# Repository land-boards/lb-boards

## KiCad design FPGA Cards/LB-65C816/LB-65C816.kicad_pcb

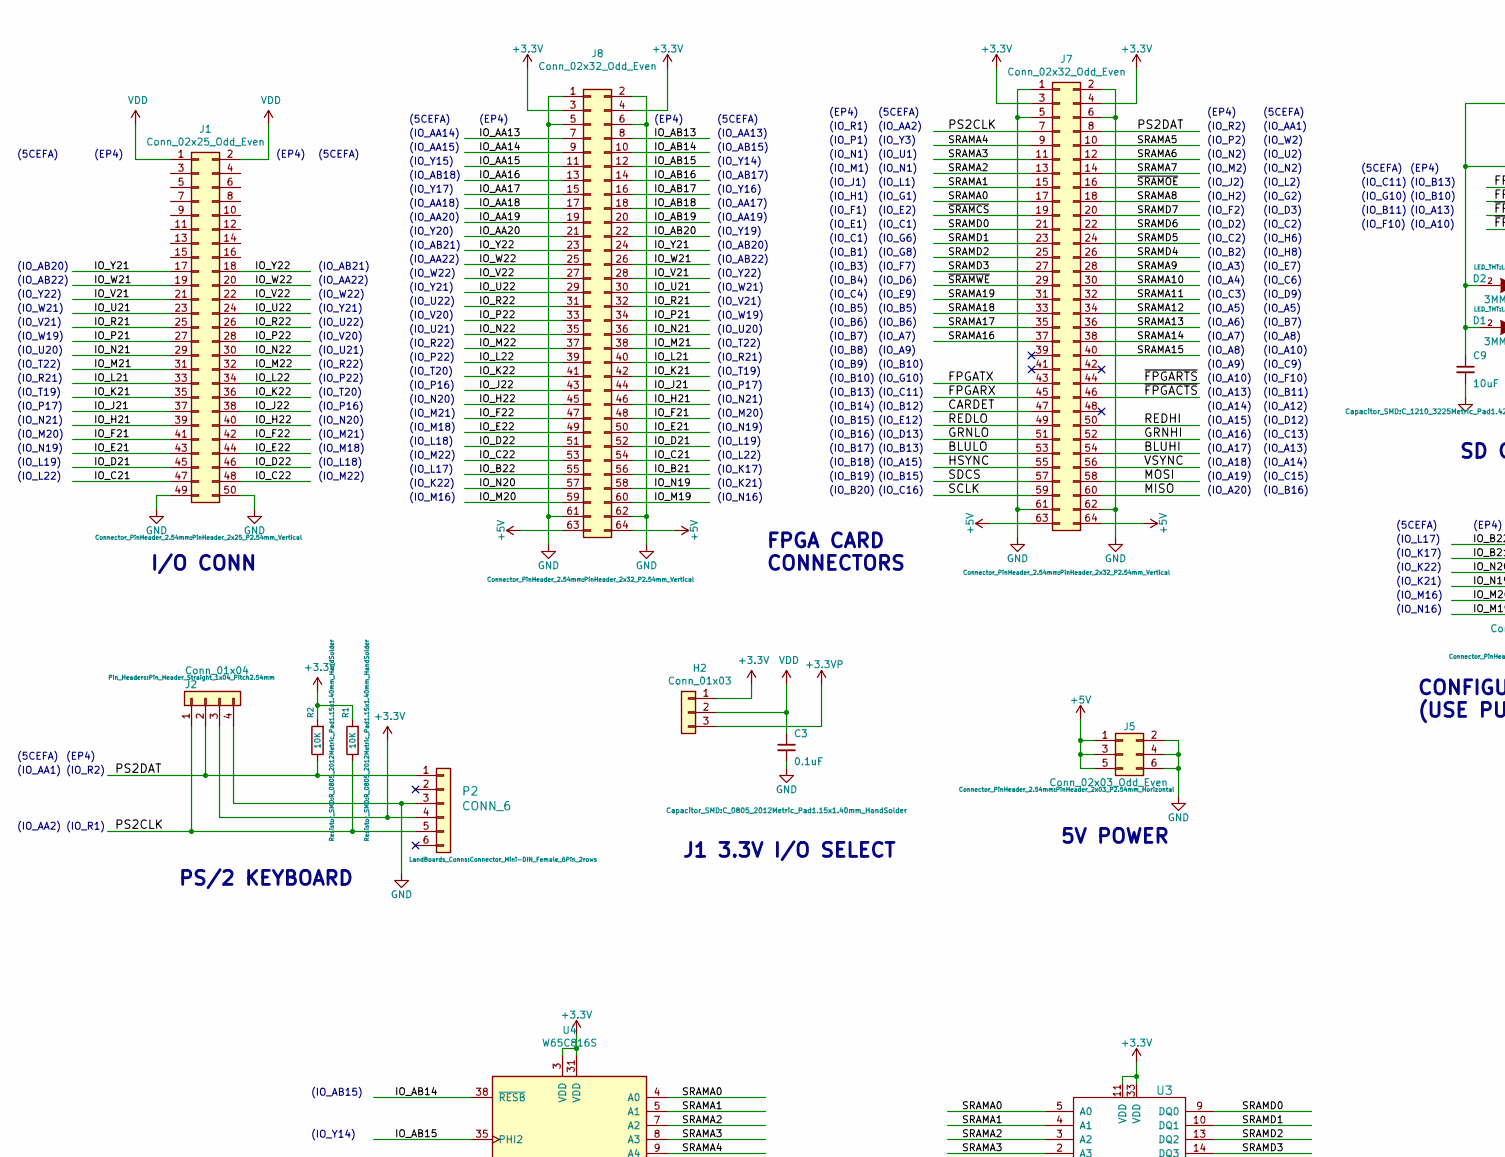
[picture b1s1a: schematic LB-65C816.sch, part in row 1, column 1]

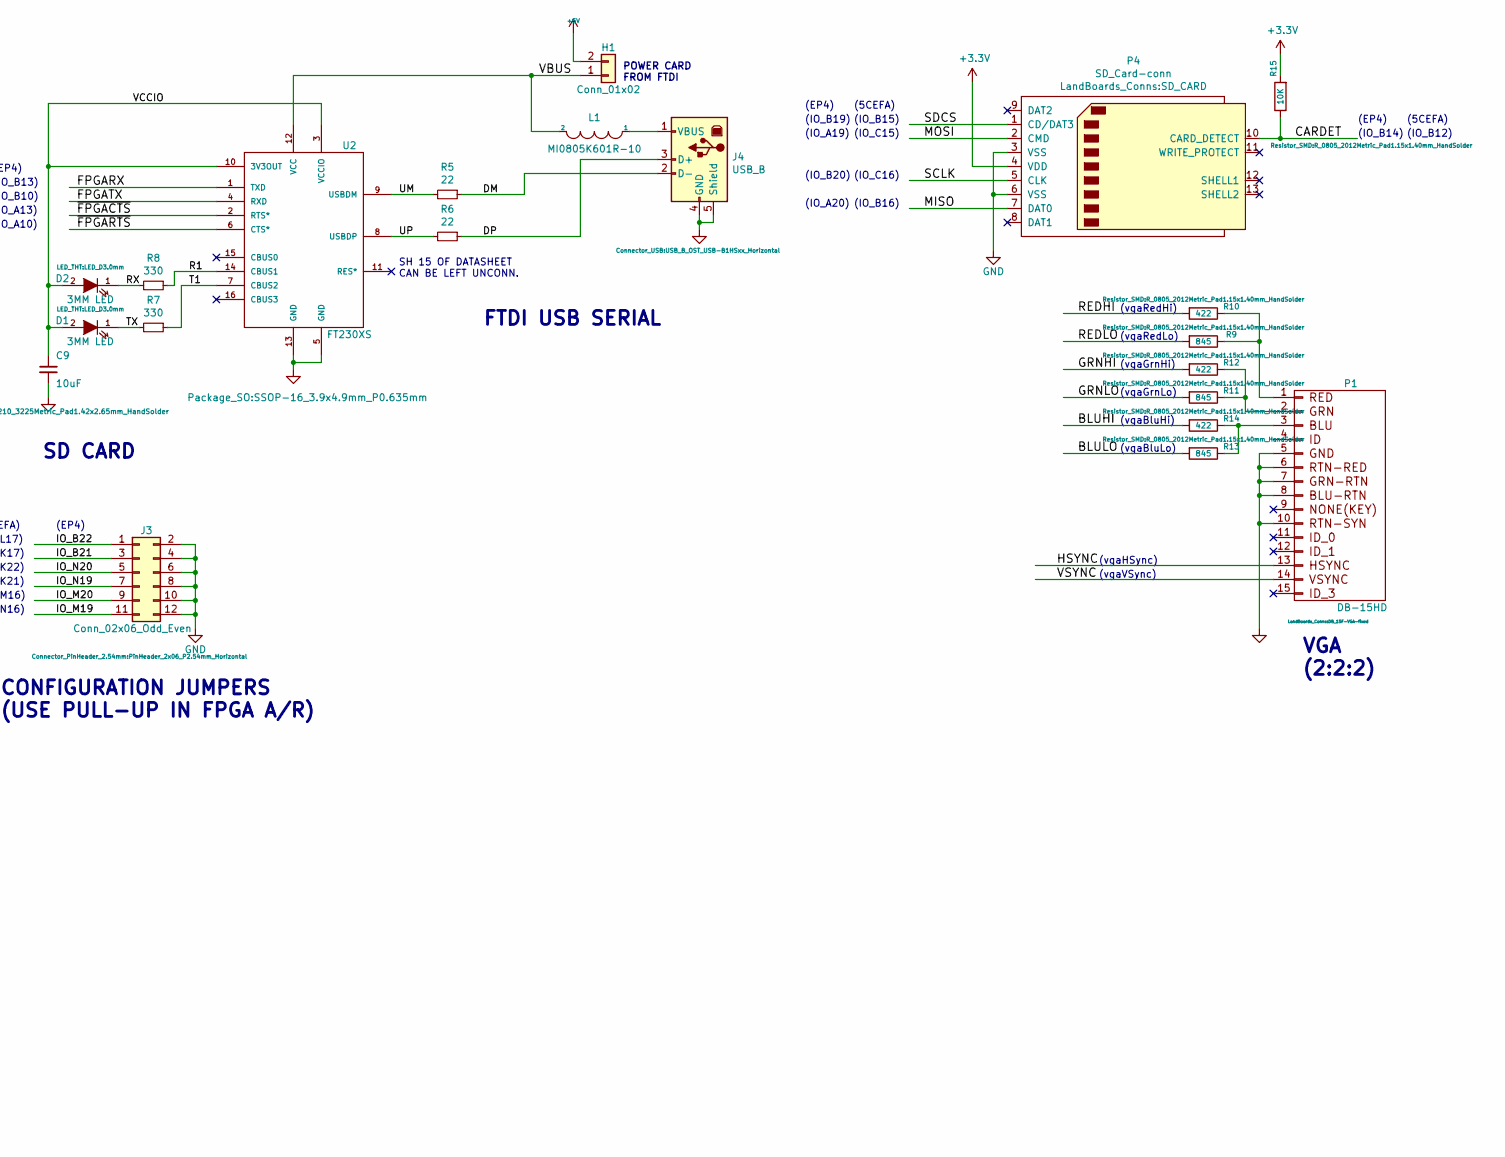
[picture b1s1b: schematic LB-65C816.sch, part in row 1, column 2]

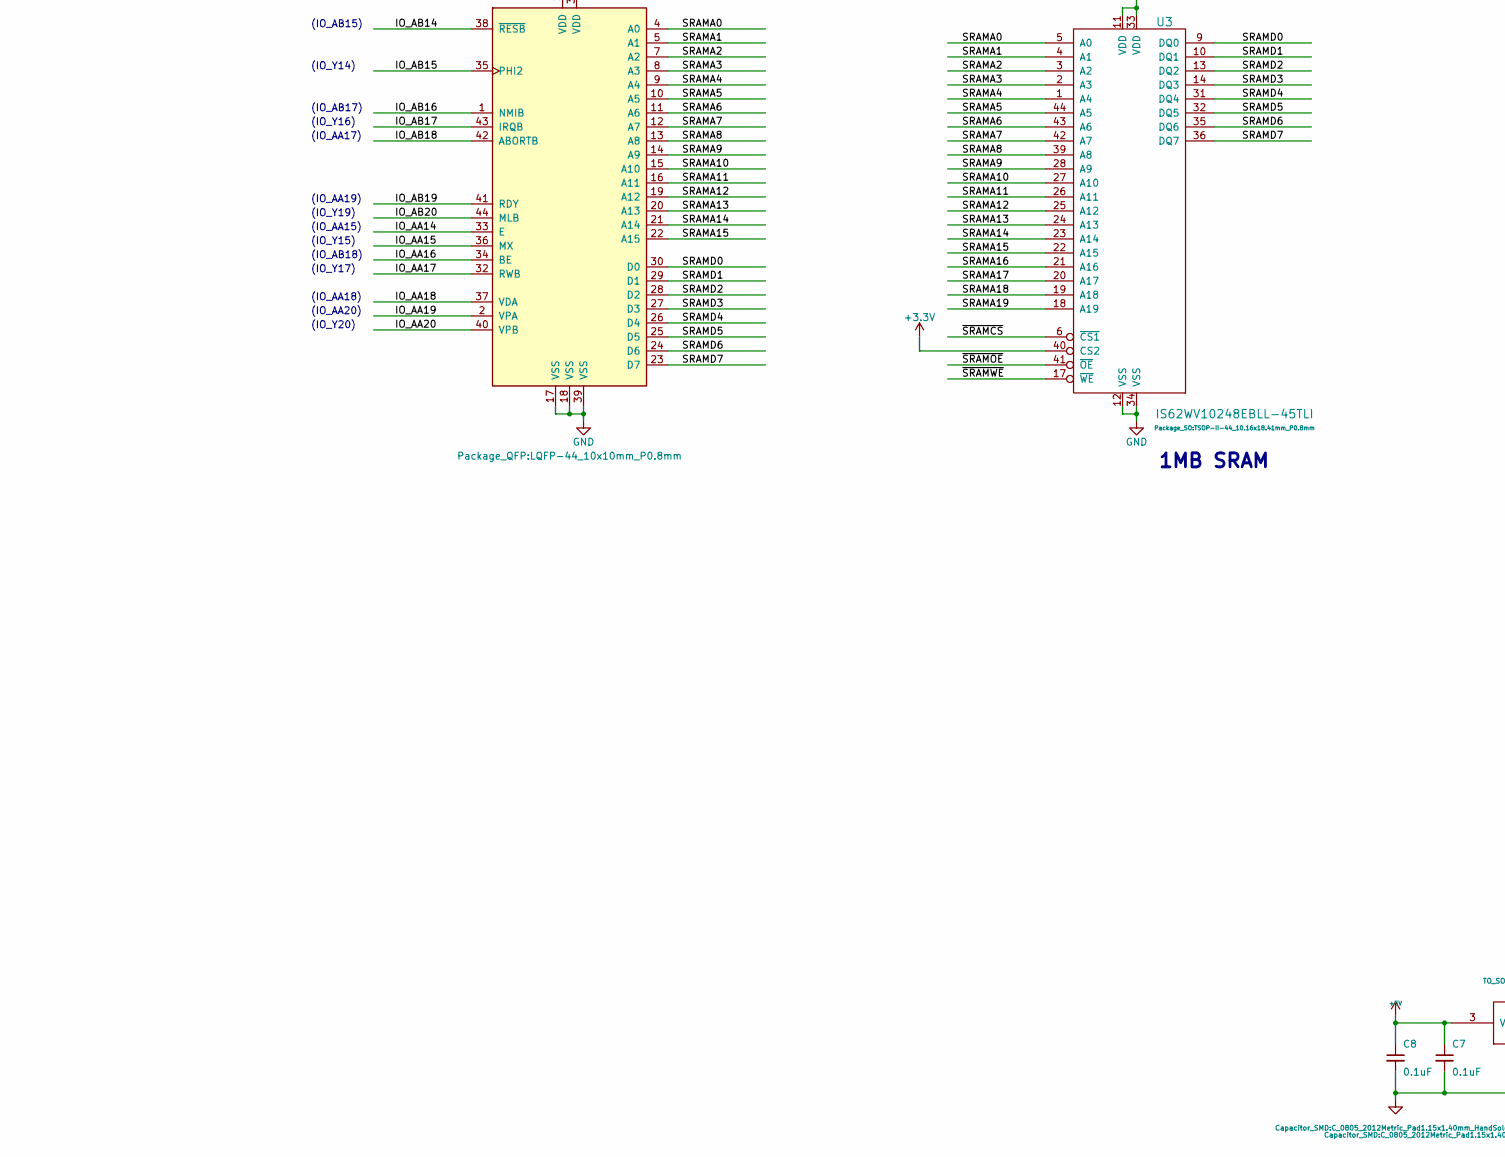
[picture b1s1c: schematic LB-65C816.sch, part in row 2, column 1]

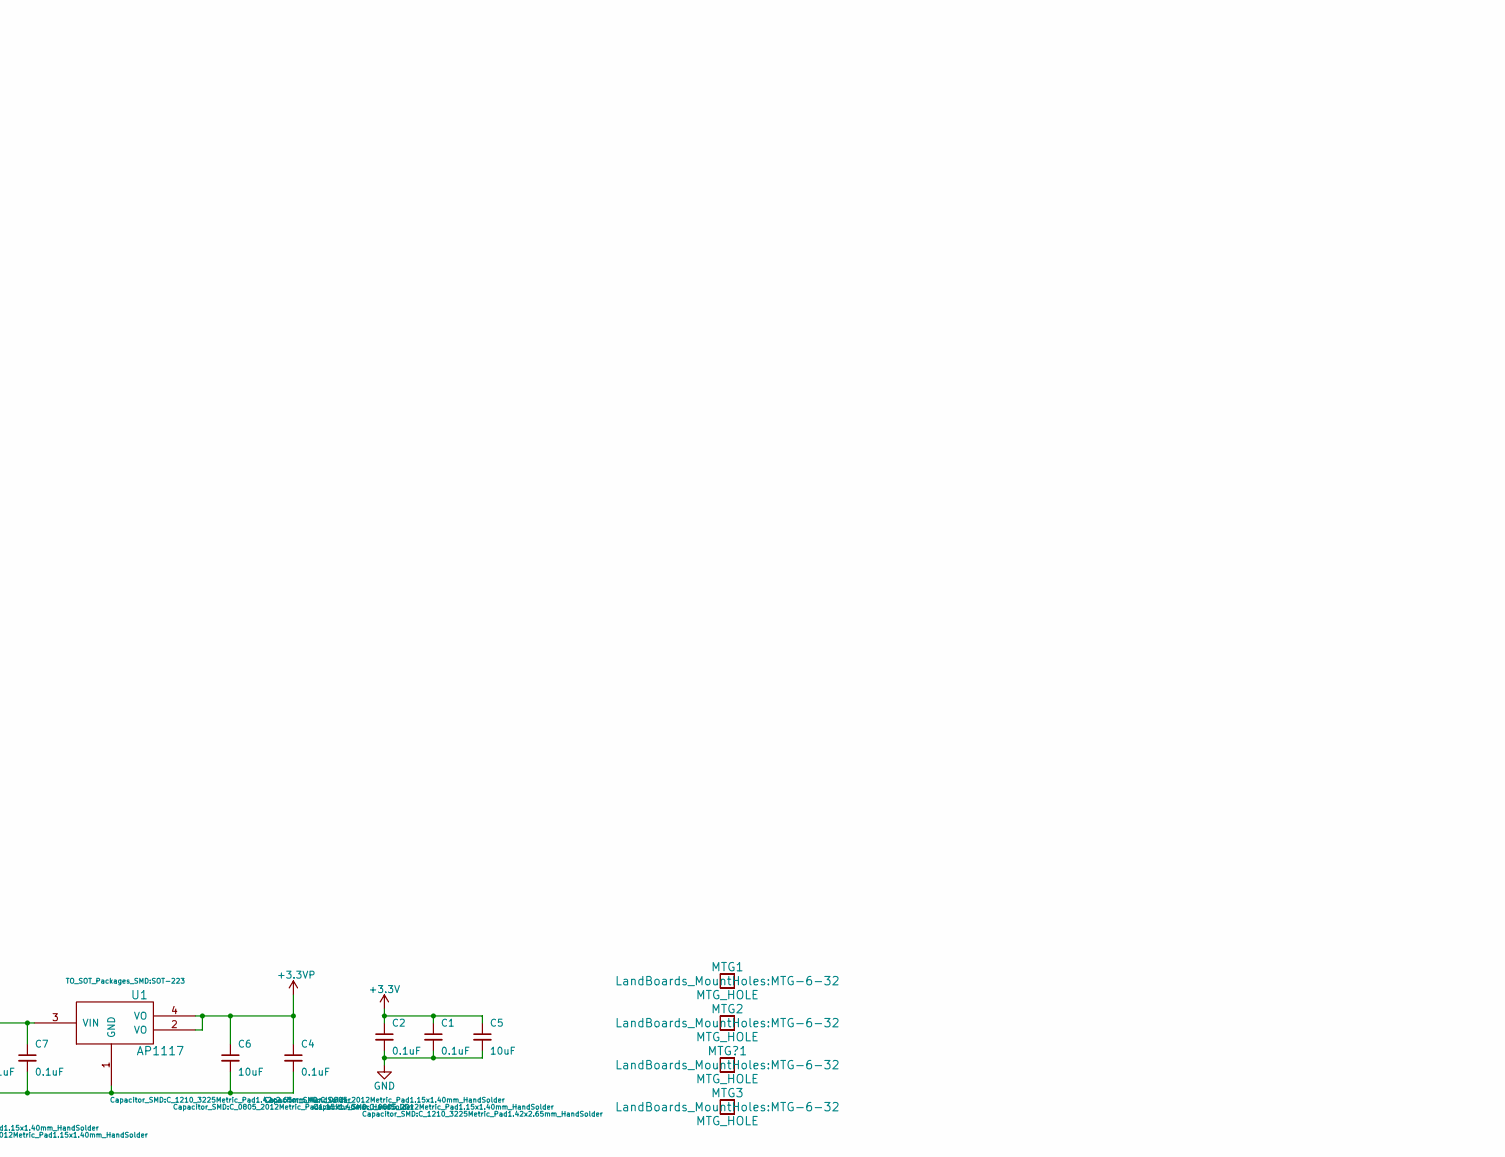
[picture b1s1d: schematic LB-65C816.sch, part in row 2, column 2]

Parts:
C1, C2, C3, C4, C7, C8: 0.1uF; C_0805_2012Metric_Pad1.15x1.40mm_HandSolder
C5, C6, C9: 10uF; C_1210_3225Metric_Pad1.42x2.65mm_HandSolder
D1, D2: 3MM LED; LED_D3.0mm
H1: Conn_01x02; Pin_Header_Straight_1x02_Pitch2.54mm
H2: Conn_01x03; PinHeader_1x03_P2.54mm_Horizontal
J1: Conn_02x25_Odd_Even; PinHeader_2x25_P2.54mm_Vertical
J2: Conn_01x04; Pin_Header_Straight_1x04_Pitch2.54mm
J3: Conn_02x06_Odd_Even; PinHeader_2x06_P2.54mm_Horizontal
J4: USB_B; USB_B_OST_USB-B1HSxx_Horizontal
J5: Conn_02x03_Odd_Even; PinHeader_2x03_P2.54mm_Horizontal
J7, J8: Conn_02x32_Odd_Even; PinHeader_2x32_P2.54mm_Vertical
L1: MI0805K601R-10; L_0805_2012Metric_Pad1.15x1.40mm_HandSolder
MTG1, MTG2, MTG3: MTG_HOLE; MTG-6-32
MTG?1: MTG_HOLE; MTG-6-32
P1: DB-15HD; DB_15F-VGA-fixed
P2: CONN_6; Connector_Mini-DIN_Female_6Pin_2rows
P4: SD_Card-conn; SD_CARD
R1, R2, R15: 10K; R_0805_2012Metric_Pad1.15x1.40mm_HandSolder
R5, R6: 22; R_0805_2012Metric_Pad1.15x1.40mm_HandSolder
R7, R8: 330; R_0805_2012Metric_Pad1.15x1.40mm_HandSolder
R9, R11, R13: 845; R_0805_2012Metric_Pad1.15x1.40mm_HandSolder
R10, R12, R14: 422; R_0805_2012Metric_Pad1.15x1.40mm_HandSolder
U1: AP1117; SOT-223
U2: FT230XS; SSOP-16_3.9x4.9mm_P0.635mm
U3: IS62WV10248EBLL-45TLI; TSOP-II-44_10.16x18.41mm_P0.8mm
U4: W65C816S; LQFP-44_10x10mm_P0.8mm

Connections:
+3.3VP: C4.1, C6.1, H2.3, U1.2 (VO), U1.4 (VO)
+3V3: C1.1, C2.1, C5.1, H2.1, J2.3, J7.3, J7.4, J8.3, J8.4, P2.4, P4.4 (VDD), R1.2, R2.2, R15.2, U3.11 (VDD), U3.33 (VDD), U3.40 (CS2), U4.3 (VDD), U4.31 (VDD)
+5V: C7.1, C8.1, H1.2, J5.1, J5.3, J5.5, J7.63, J7.64, J8.63, J8.64, U1.3 (VIN)
/BLUHI: J7.54, R14.2
/BLULO: J7.53, R13.2
/CARDET: J7.47, P4.10 (CARD_DETECT), R15.1
/DM: J4.2 (D-), R5.1
/DP: J4.3 (D+), R6.1
/FPGARX: J7.45, U2.1 (TXD)
/FPGATX: J7.43, U2.4 (RXD)
/GRNHI: J7.52, R12.2
/GRNLO: J7.51, R11.2
/HSYNC: J7.55, P1.13
/IO_AA14: J8.9, U4.33 (E)
/IO_AA15: J8.11, U4.36 (MX)
/IO_AA16: J8.13, U4.34 (BE)
/IO_AA17: J8.15, U4.32 (RWB)
/IO_AA18: J8.17, U4.37 (VDA)
/IO_AA19: J8.19, U4.2 (VPA)
/IO_AA20: J8.21, U4.40 (VPB)
/IO_AB14: J8.10, U4.38 (~RESB)
/IO_AB15: J8.12, U4.35 (PHI2)
/IO_AB16: J8.14, U4.1 (NMIB)
/IO_AB17: J8.16, U4.43 (IRQB)
/IO_AB18: J8.18, U4.42 (ABORTB)
/IO_AB19: J8.20, U4.41 (RDY)
/IO_AB20: J8.22, U4.44 (MLB)
/IO_B21: J3.3, J8.56
/IO_B22: J3.1, J8.55
/IO_C21: J1.47, J8.54
/IO_C22: J1.48, J8.53
/IO_D21: J1.45, J8.52
/IO_D22: J1.46, J8.51
/IO_E21: J1.43, J8.50
/IO_E22: J1.44, J8.49
/IO_F21: J1.41, J8.48
/IO_F22: J1.42, J8.47
/IO_H21: J1.39, J8.46
/IO_H22: J1.40, J8.45
/IO_J21: J1.37, J8.44
/IO_J22: J1.38, J8.43
/IO_K21: J1.35, J8.42
/IO_K22: J1.36, J8.41
/IO_L21: J1.33, J8.40
/IO_L22: J1.34, J8.39
/IO_M19: J3.11, J8.60
/IO_M20: J3.9, J8.59
/IO_M21: J1.31, J8.38
/IO_M22: J1.32, J8.37
/IO_N19: J3.7, J8.58
/IO_N20: J3.5, J8.57
/IO_N21: J1.29, J8.36
/IO_N22: J1.30, J8.35
/IO_P21: J1.27, J8.34
/IO_P22: J1.28, J8.33
/IO_R21: J1.25, J8.32
/IO_R22: J1.26, J8.31
/IO_U21: J1.23, J8.30
/IO_U22: J1.24, J8.29
/IO_V21: J1.21, J8.28
/IO_V22: J1.22, J8.27
/IO_W21: J1.19, J8.26
/IO_W22: J1.20, J8.25
/IO_Y21: J1.17, J8.24
/IO_Y22: J1.18, J8.23
/MISO: J7.60, P4.7 (DAT0)
/MOSI: J7.58, P4.2 (CMD)
/PS2CLK: J2.1, J7.7, P2.5, R1.1
/PS2DAT: J2.2, J7.8, P2.1, R2.1
/R1: R8.1, U2.14 (CBUS1)
/REDHI: J7.50, R10.2
/REDLO: J7.49, R9.2
/RX: D2.1 (K), R8.2
/SCLK: J7.59, P4.5 (CLK)
/SDCS: J7.57, P4.1 (CD/DAT3)
/SRAMA0: J7.17, U3.5 (A0), U4.4 (A0)
/SRAMA1: J7.15, U3.4 (A1), U4.5 (A1)
/SRAMA2: J7.13, U3.3 (A2), U4.7 (A2)
/SRAMA3: J7.11, U3.2 (A3), U4.8 (A3)
/SRAMA4: J7.9, U3.1 (A4), U4.9 (A4)
/SRAMA5: J7.10, U3.44 (A5), U4.10 (A5)
/SRAMA6: J7.12, U3.43 (A6), U4.11 (A6)
/SRAMA7: J7.14, U3.42 (A7), U4.12 (A7)
/SRAMA8: J7.18, U3.39 (A8), U4.13 (A8)
/SRAMA9: J7.28, U3.28 (A9), U4.14 (A9)
/SRAMA10: J7.30, U3.27 (A10), U4.15 (A10)
/SRAMA11: J7.32, U3.26 (A11), U4.16 (A11)
/SRAMA12: J7.34, U3.25 (A12), U4.19 (A12)
/SRAMA13: J7.36, U3.24 (A13), U4.20 (A13)
/SRAMA14: J7.38, U3.23 (A14), U4.21 (A14)
/SRAMA15: J7.40, U3.22 (A15), U4.22 (A15)
/SRAMA16: J7.37, U3.21 (A16)
/SRAMA17: J7.35, U3.20 (A17)
/SRAMA18: J7.33, U3.19 (A18)
/SRAMA19: J7.31, U3.18 (A19)
/SRAMD0: J7.21, U3.9 (DQ0), U4.30 (D0)
/SRAMD1: J7.23, U3.10 (DQ1), U4.29 (D1)
/SRAMD2: J7.25, U3.13 (DQ2), U4.28 (D2)
/SRAMD3: J7.27, U3.14 (DQ3), U4.27 (D3)
/SRAMD4: J7.26, U3.31 (DQ4), U4.26 (D4)
/SRAMD5: J7.24, U3.32 (DQ5), U4.25 (D5)
/SRAMD6: J7.22, U3.35 (DQ6), U4.24 (D6)
/SRAMD7: J7.20, U3.36 (DQ7), U4.23 (D7)
/T1: R7.1, U2.7 (CBUS2)
/TX: D1.1 (K), R7.2
/UM: R5.2, U2.9 (USBDM)
/UP: R6.2, U2.8 (USBDP)
/VBUS: H1.1, L1.2, U2.12 (VCC)
/VCCIO: C9.1, D1.2 (A), D2.2 (A), U2.3 (VCCIO), U2.10 (3V3OUT)
/VSYNC: J7.56, P1.14
/~FPGACTS: J7.46, U2.2 (RTS*)
/~FPGARTS: J7.44, U2.6 (CTS*)
/~SRAMCS: J7.19, U3.6 (~CS1)
/~SRAMOE: J7.16, U3.41 (~OE)
/~SRAMWE: J7.29, U3.17 (~WE)
GND: C1.2, C2.2, C3.2, C4.2, C5.2, C6.2, C7.2, C8.2, C9.2, J1.49, J1.50, J2.4, J3.2, J3.4, J3.6, J3.8, J3.10, J3.12, J4.4 (GND), J4.5 (Shield), J5.2, J5.4, J5.6, J7.1, J7.2, J7.5, J7.6, J7.61, J7.62, J8.1, J8.2, J8.5, J8.6, J8.61, J8.62, P1.5, P1.6, P1.7, P1.8, P1.10, P2.3, P4.3 (VSS), P4.6 (VSS), U1.1 (GND), U2.5 (GND), U2.13 (GND), U3.12 (VSS), U3.34 (VSS), U4.17 (VSS), U4.18 (VSS), U4.39 (VSS)
unnamed: J4.1 (VBUS), L1.1
unnamed: P1.1, R9.1, R10.1
unnamed: P1.2, R11.1, R12.1
unnamed: P1.3, R13.1, R14.1
VDD: C3.1, H2.2, J1.1, J1.2

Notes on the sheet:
SD CARD
I/O CONN
PS/2 KEYBOARD
FTDI USB SERIAL
VGA (2:2:2)
FPGA CARD CONNECTORS
(vgaRedHi)
(vgaRedLo)
(vgaGrnHi)
(vgaGrnLo)
(vgaBluHi)
(vgaBluLo)
(vgaHSync)
(vgaVSync)
POWER CARD FROM FTDI
SH 15 OF DATASHEET CAN BE LEFT UNCONN.
(IO_B5)
(IO_B6)
(IO_B7)
(IO_B8)
(IO_B9)
(IO_B10)
(IO_B13)
(IO_B14)
(IO_B15)
(IO_B16)
(IO_B17)
(IO_B18)
(IO_B19)
(IO_B20)
(IO_P2)
(IO_N2)
(IO_A15)
(IO_A16)
1MB SRAM
(IO_R1)
(IO_P1)
(IO_N1)
(IO_M1)
(IO_J1)

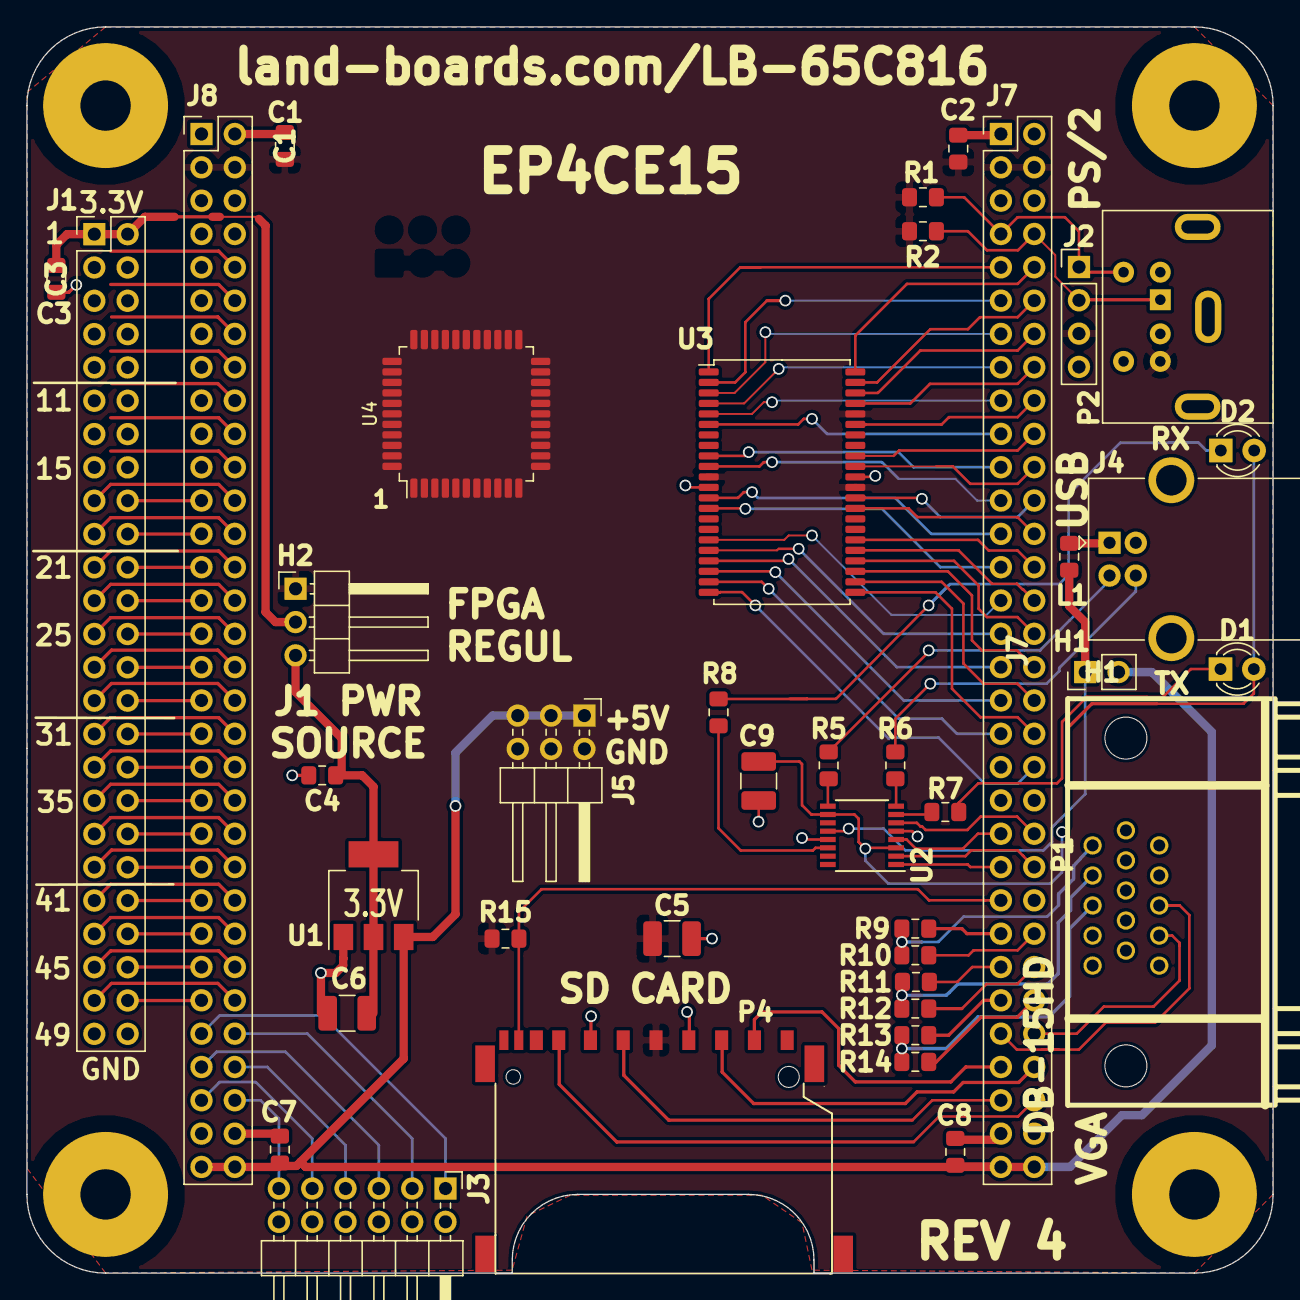
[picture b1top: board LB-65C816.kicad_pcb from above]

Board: 2 copper layers, 95.0 x 95.0 mm, 45 parts (0 on the bottom side), 121 nets.

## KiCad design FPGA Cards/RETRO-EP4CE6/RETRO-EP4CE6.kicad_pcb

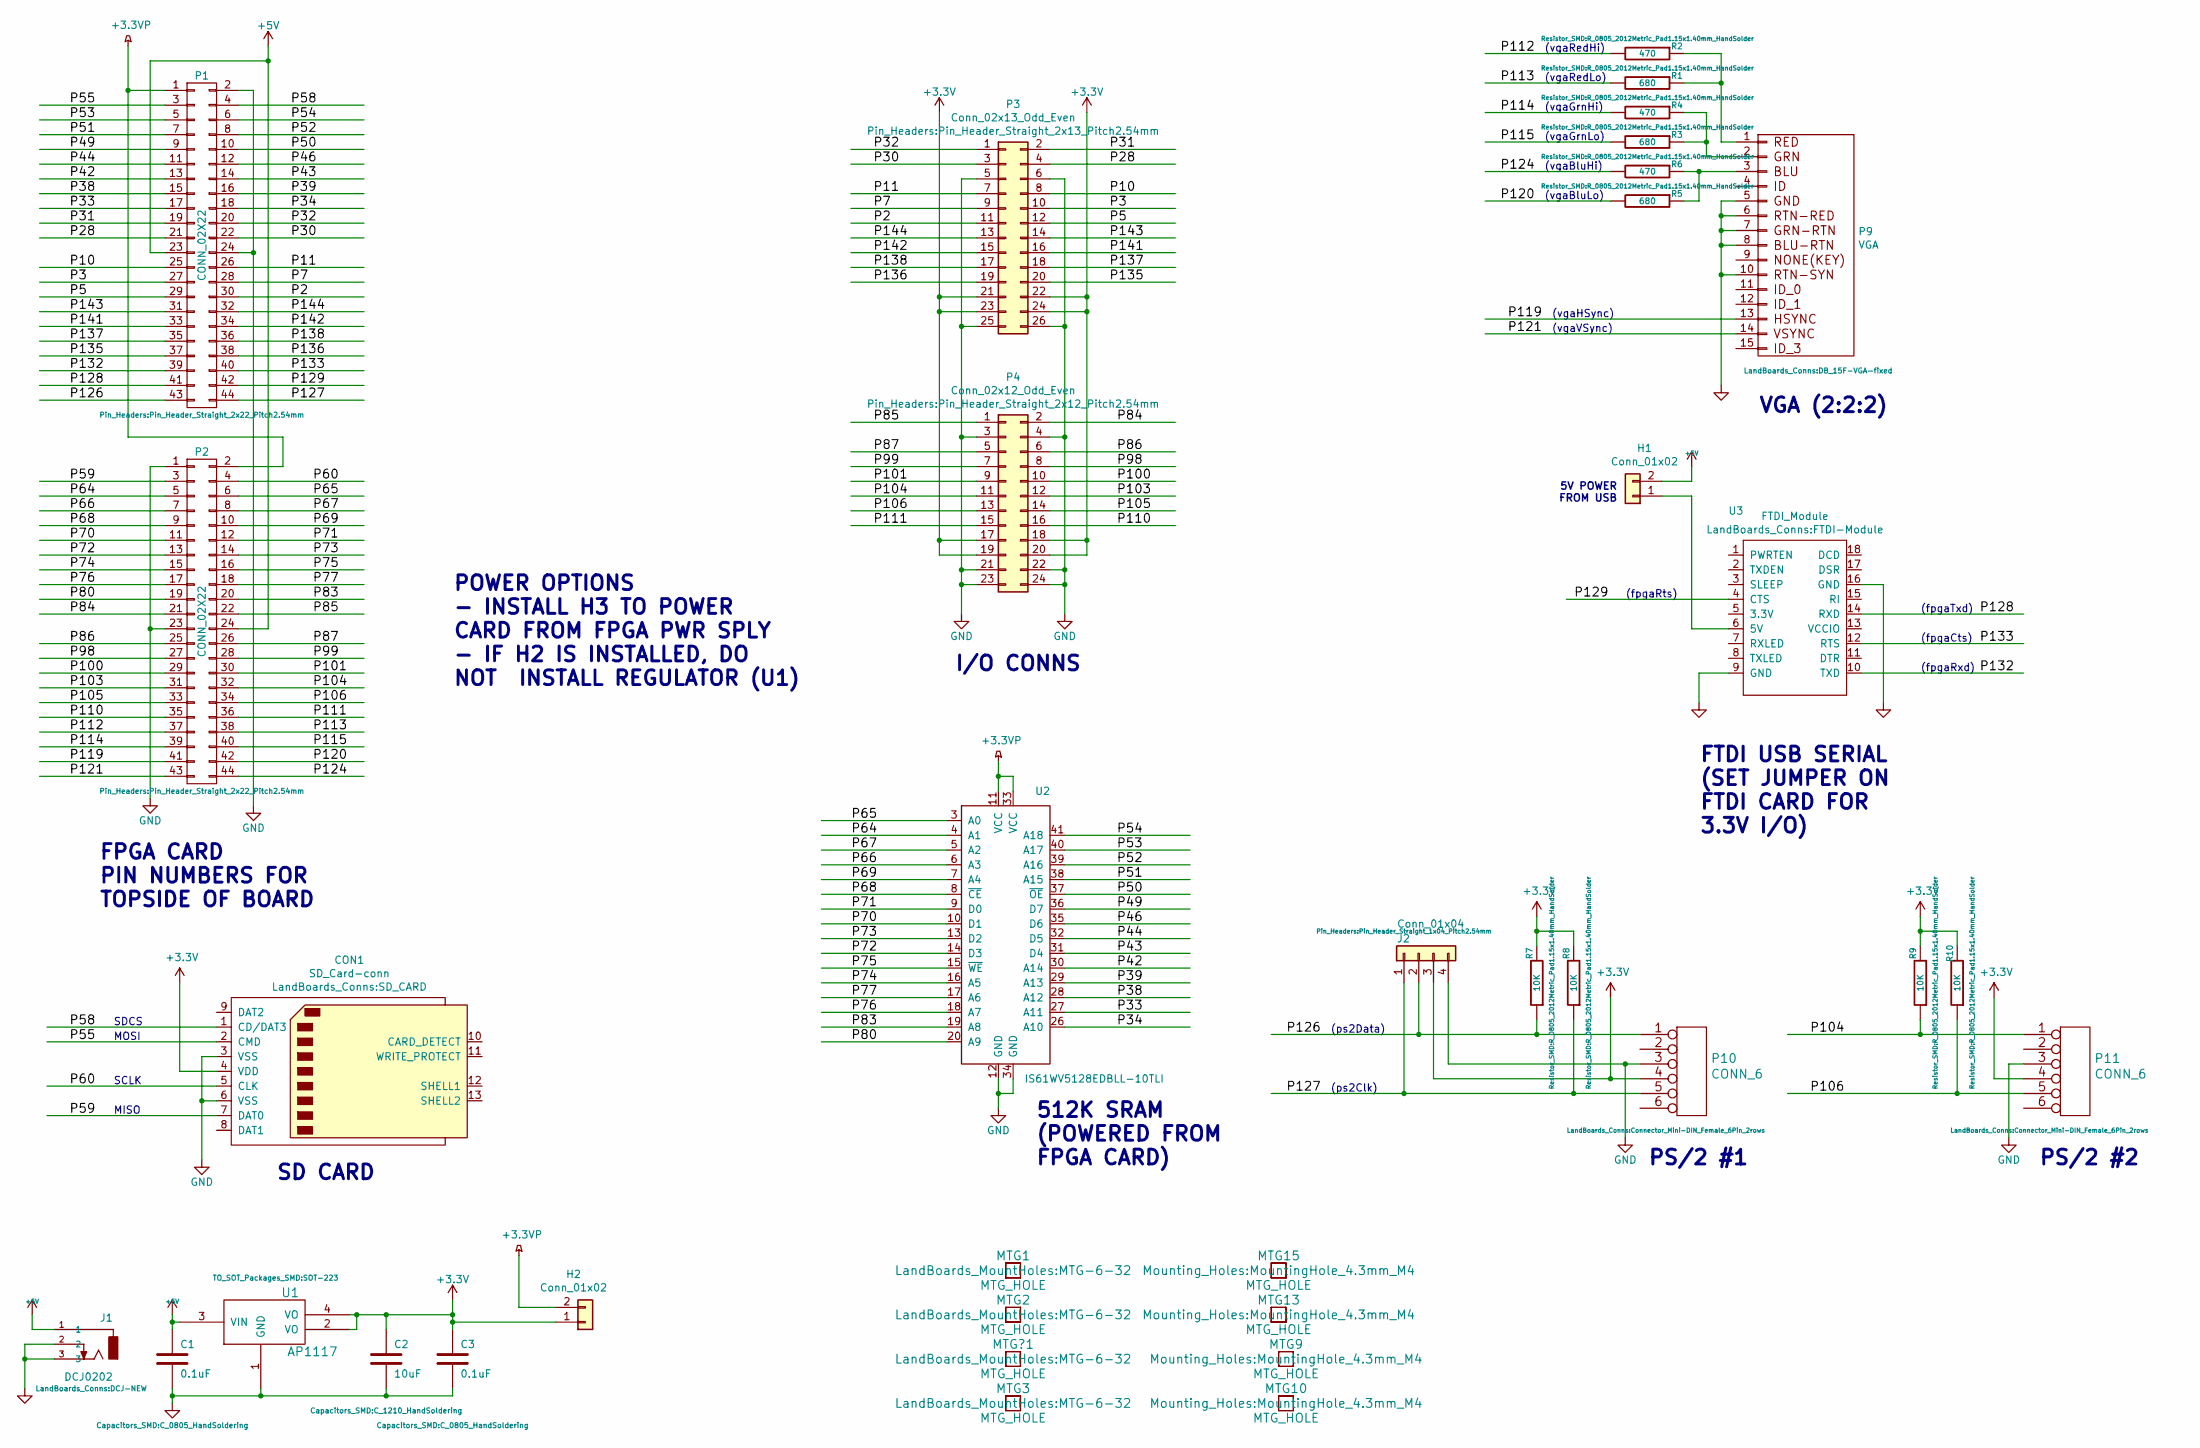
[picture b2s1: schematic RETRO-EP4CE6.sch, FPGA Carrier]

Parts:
C1, C3: 0.1uF; C_0805_HandSoldering
C2: 10uF; C_1210_HandSoldering
CON1: SD_Card-conn; SD_CARD
H1: Conn_01x02; Pin_Header_Straight_1x02_Pitch2.54mm
H2: Conn_01x02; PinHeader_1x02_P2.54mm_Horizontal
J1: DCJ0202; DCJ-NEW
J2: Conn_01x04; Pin_Header_Straight_1x04_Pitch2.54mm
MTG1, MTG2, MTG3: MTG_HOLE; MTG-6-32
MTG9, MTG10, MTG13, MTG15: MTG_HOLE; MountingHole_4.3mm_M4
MTG?1: MTG_HOLE; MTG-6-32
P1, P2: CONN_02X22; Pin_Header_Straight_2x22_Pitch2.54mm
P3: Conn_02x13_Odd_Even; Pin_Header_Straight_2x13_Pitch2.54mm
P4: Conn_02x12_Odd_Even; Pin_Header_Straight_2x12_Pitch2.54mm
P9: VGA; DB_15F-VGA-fixed
P10, P11: CONN_6; Connector_Mini-DIN_Female_6Pin_2rows
R1, R3, R5: 680; R_0805_2012Metric_Pad1.15x1.40mm_HandSolder
R2, R4, R6: 470; R_0805_2012Metric_Pad1.15x1.40mm_HandSolder
R7, R8, R9, R10: 10K; R_0805_2012Metric_Pad1.15x1.40mm_HandSolder
U1: AP1117; SOT-223
U2: IS61WV5128EDBLL-10TLI; TSOP-II-44_10.16x18.41mm_P0.8mm
U3: FTDI_Module; FTDI-Module

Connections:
+3.3VP: H2.2, P1.1, P2.2, U2.11 (VCC), U2.33 (VCC)
+3V3: C2.1, C3.1, CON1.4 (VDD), H2.1, J2.3, P3.21, P3.22, P3.23, P3.24, P4.17, P4.18, P4.19, P4.20, P10.4, P11.4, R7.2, R8.2, R9.2, R10.2, U1.2 (VO), U1.4 (VO)
+5V: C1.1, H1.2, J1.1, P1.23, P2.24, U1.3 (VIN)
/P2: P1.30, P3.11
/P3: P1.27, P3.10
/P5: P1.29, P3.12
/P7: P1.28, P3.9
/P10: P1.25, P3.8
/P11: P1.26, P3.7
/P28: P1.21, P3.4
/P30: P1.22, P3.3
/P31: P1.19, P3.2
/P32: P1.20, P3.1
/P33: P1.17, U2.27 (A11)
/P34: P1.18, U2.26 (A10)
/P38: P1.15, U2.28 (A12)
/P39: P1.16, U2.29 (A13)
/P42: P1.13, U2.30 (A14)
/P43: P1.14, U2.31 (D4)
/P44: P1.11, U2.32 (D5)
/P46: P1.12, U2.35 (D6)
/P49: P1.9, U2.36 (D7)
/P50: P1.10, U2.37 (~OE)
/P51: P1.7, U2.38 (A15)
/P52: P1.8, U2.39 (A16)
/P53: P1.5, U2.40 (A17)
/P54: P1.6, U2.41 (A18)
/P55: CON1.2 (CMD), P1.3
/P58: CON1.1 (CD/DAT3), P1.4
/P59: CON1.7 (DAT0), P2.3
/P60: CON1.5 (CLK), P2.4
/P64: P2.5, U2.4 (A1)
/P65: P2.6, U2.3 (A0)
/P66: P2.7, U2.6 (A3)
/P67: P2.8, U2.5 (A2)
/P68: P2.9, U2.8 (~CE)
/P69: P2.10, U2.7 (A4)
/P70: P2.11, U2.10 (D1)
/P71: P2.12, U2.9 (D0)
/P72: P2.13, U2.14 (D3)
/P73: P2.14, U2.13 (D2)
/P74: P2.15, U2.16 (A5)
/P75: P2.16, U2.15 (~WE)
/P76: P2.17, U2.18 (A7)
/P77: P2.18, U2.17 (A6)
/P80: P2.19, U2.20 (A9)
/P83: P2.20, U2.19 (A8)
/P84: P2.21, P4.2
/P85: P2.22, P4.1
/P86: P2.25, P4.6
/P87: P2.26, P4.5
/P98: P2.27, P4.8
/P99: P2.28, P4.7
/P100: P2.29, P4.10
/P101: P2.30, P4.9
/P103: P2.31, P4.12
/P104: P2.32, P4.11, P11.1, R9.1
/P105: P2.33, P4.14
/P106: P2.34, P4.13, P11.5, R10.1
/P110: P2.35, P4.16
/P111: P2.36, P4.15
/P112: P2.37, R2.2
/P113: P2.38, R1.2
/P114: P2.39, R4.2
/P115: P2.40, R3.2
/P119: P2.41, P9.13
/P120: P2.42, R5.2
/P121: P2.43, P9.14
/P124: P2.44, R6.2
/P126: J2.2, P1.43, P10.1, R7.1
/P127: J2.1, P1.44, P10.5, R8.1
/P128: P1.41, U3.14 (RXD)
/P129: P1.42, U3.4 (CTS)
/P132: P1.39, U3.10 (TXD)
/P133: P1.40, U3.12 (RTS)
/P135: P1.37, P3.20
/P136: P1.38, P3.19
/P137: P1.35, P3.18
/P138: P1.36, P3.17
/P141: P1.33, P3.16
/P142: P1.34, P3.15
/P143: P1.31, P3.14
/P144: P1.32, P3.13
GND: C1.2, C2.2, C3.2, CON1.3 (VSS), CON1.6 (VSS), J1.2, J1.3, J2.4, P1.2, P1.24, P2.1, P2.23, P3.5, P3.6, P3.25, P3.26, P4.3, P4.4, P4.21, P4.22, P4.23, P4.24, P9.5, P9.6, P9.7, P9.8, P9.10, P10.3, P11.3, U1.1 (GND), U2.12 (GND), U2.34 (GND), U3.9 (GND), U3.16 (GND)
unnamed: H1.1, U3.6 (5V)
unnamed: P9.1, R1.1, R2.1
unnamed: P9.2, R3.1, R4.1
unnamed: P9.3, R5.1, R6.1

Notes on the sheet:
(ps2Data)
(ps2Clk)
512K SRAM (POWERED FROM FPGA CARD)
SD CARD
I/O CONNS
PS/2 #1
FTDI USB SERIAL (SET JUMPER ON FTDI CARD FOR 3.3V I/O)
VGA (2:2:2)
FPGA CARD PIN NUMBERS FOR TOPSIDE OF BOARD
(vgaRedHi)
(vgaRedLo)
(vgaGrnHi)
(vgaGrnLo)
(vgaBluHi)
(vgaBluLo)
(vgaHSync)
(vgaVSync)
(fpgaRts)
(fpgaTxd)
(fpgaCts)
(fpgaRxd)
5V POWER FROM USB
SDCS
MOSI
SCLK
MISO
PS/2 #2
POWER OPTIONS - INSTALL H3 TO POWER CARD FROM FPGA PWR SPLY - IF H2 IS INSTALLED, DO NOT INSTALL REGULATOR (U1)

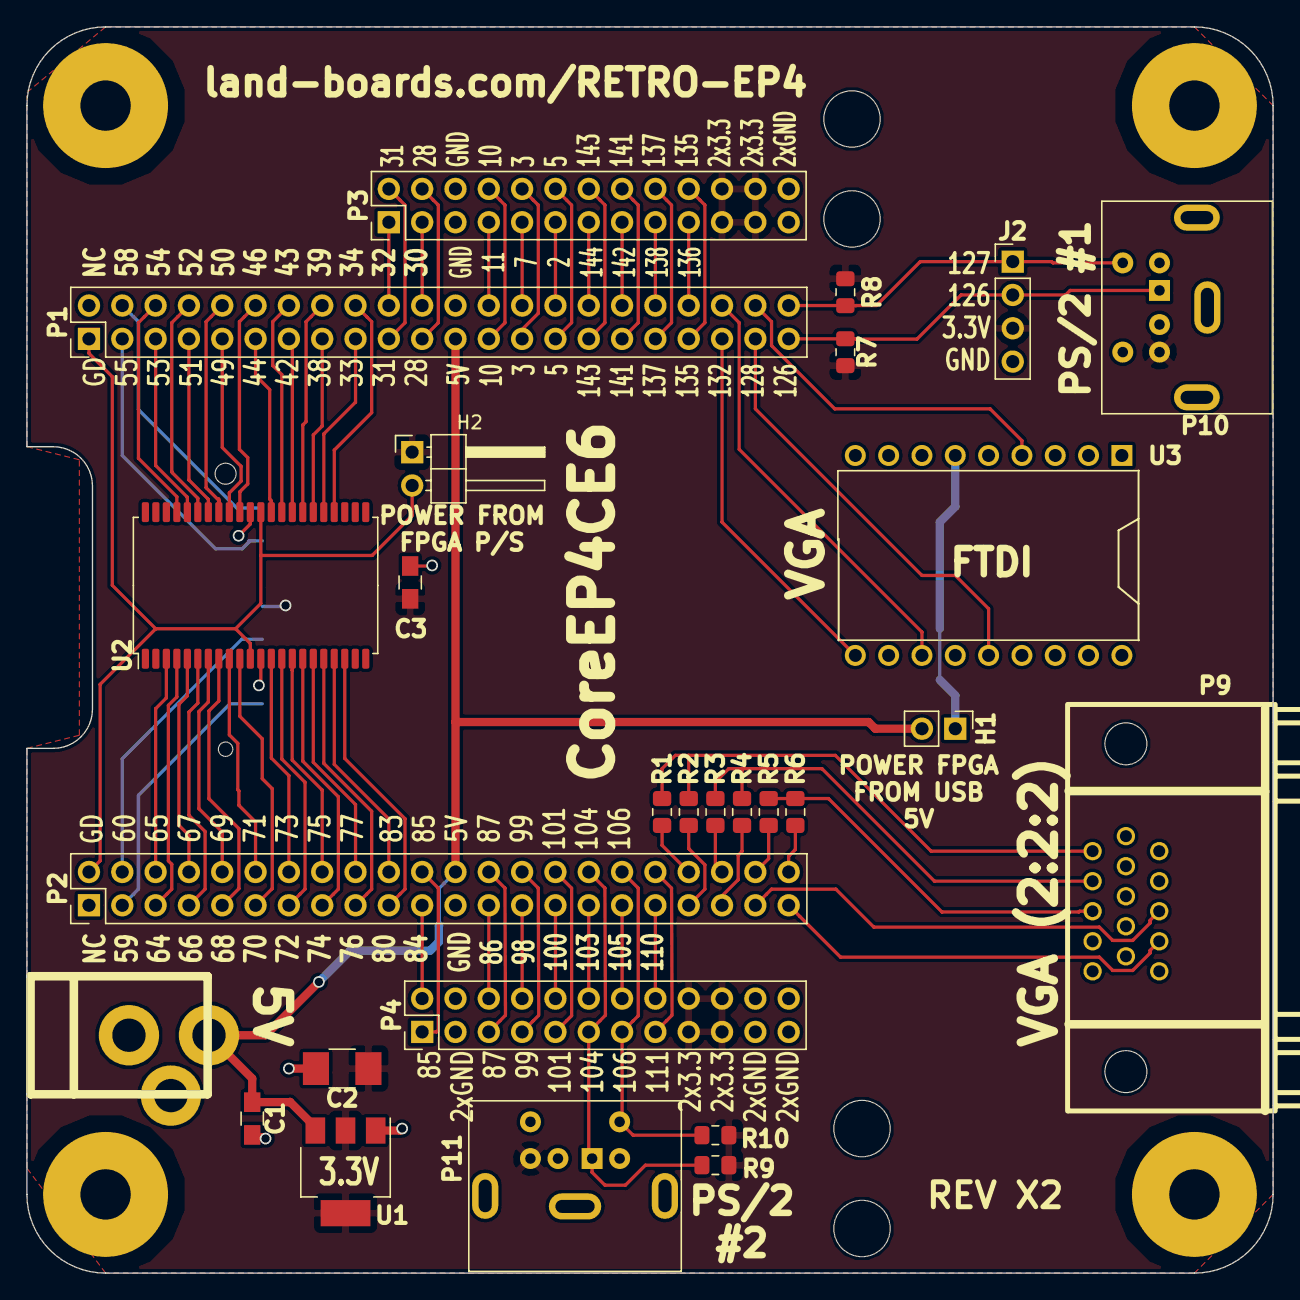
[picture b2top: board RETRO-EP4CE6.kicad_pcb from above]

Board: 2 copper layers, 95.0 x 95.0 mm, 36 parts (1 on the bottom side), 88 nets.
